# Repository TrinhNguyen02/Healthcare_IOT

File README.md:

# Healthcare_IOT
Overview:
Real time 
IoT Based Patient Health Monitoring System on ESP8266/ESP32 using MAX30100/102 Pulse Oximeter, DS18B20 temperature, DHT11 Humidity & Temperature sensors and display OLED 0.96" . This system will Monitor the Health Status of Patient on ESP8266/ESP32 Web Server.

Reference: 
https://iotprojectsideas.com/iot-based-patient-health-monitoring-system-esp8266-esp32/

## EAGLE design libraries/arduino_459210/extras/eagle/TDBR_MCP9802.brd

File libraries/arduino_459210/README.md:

# MCP9802 DRIVER

&nbsp;&nbsp;&nbsp;&nbsp;&nbsp;&nbsp;&nbsp;&nbsp;&nbsp;&nbsp;

&nbsp;&nbsp;&nbsp;&nbsp;&nbsp;&nbsp;&nbsp;&nbsp;&nbsp;&nbsp;

&nbsp;&nbsp;&nbsp;&nbsp;&nbsp;&nbsp;&nbsp;&nbsp;&nbsp;&nbsp;

## INTRODUCTION

The MCP9802 is a 9 to 12-Bit Single-Channel Temperature Sensor with Hysteresis & Alert capabilities,  
as well as a hardware I2C interface.

This library contains a robust driver for the MCP9802 that exposes its entire functionality (i.e. Configuration, Temperature, Hysteresis, Limit, and Alert Settings), allowing the user to get/set data in degrees Celsius or Fahrenheit.

[MCP9802 DATASHEET](http://ww1.microchip.com/downloads/en/DeviceDoc/21909d.pdf)

[MCP9802 DATASHEET ERRATA](http://ww1.microchip.com/downloads/en/DeviceDoc/80331B.pdf)

## REPOSITORY CONTENTS

- **MCP9802.h** - Library Header file.
- **MCP9802.cpp** - Library Compilation.
- **/utility** 
  - **MCP9802InfoStr.h** - Header file containing a functional extention of the library to include generating printable information String (see Note #8 below).
  - **MCP9802ComStr.h** - Header file containing a functional extention of the library to include generating a printable I2C Communication Result String (see Note #9 below).
  - **MCP9802_PString.h** - Header file for PString class (lighter alternative to String class) 
  - **MCP9802_PString.cpp** - Compilation file for PString class (lighter alternative to String class) 
- **/examples**  
  - **/MCP9802_Test**
    - **MCP9802_Test.ino** - A basic sketch for testing whether the MCP9802 is hooked-up and operating correctly.
  - **/MCP9802_Usage**
    - **MCP9802_Usage.ino** - A much more extensive sketch offering a complete usage illustration, as well as a rubust testing mechanism.
  - **/MCP9802_Info**
    - **MCP9802_Info.ino** - A short sketch showing how to generate a Printable Device Information String of the MCP9802's current settings (i.e. Configuration, Limit &anp; Hysteresis registers, etc.).
  - **/MCP9802_I2C_Status**
    - **MCP9802_I2C_Status.ino** - A short sketch for verifying I2C communication has been established between the controller and the MCP9802.
- **/extras** 
  - **License.txt** - A cope of the end-user license agreement.  
  - **/eagle**
    - **MCP9802.sch** - Schematic file for the MCP9802 breakout board.
    - **MCP9802.brd** - Board layout file for the MCP9802 breakout board.
- **keywords.txt** - Keywords for this library which will be highlighted in sketches within the Arduino IDE. 
- **library.properties** - General library properties for the Arduino's IDE (>1.5) Library Package Manager.
- **README.md** - The readme file for this library.
- **library.json** - JSON file for the Arduino's IDE (>1.5) Package Manager.

## HOOK-UP

* __PIN 1 (VCC)__ - Connect VCC to the Arduino's 5V output
* __PIN 2 (GND)__ - Connect GND to the Arduino's GND
* __PIN 3 (ALERT)__ - Connect ALERT to the Arduino's Digital Pin 2
* __PIN 4 (SCL)__ - Connect SCL to the Arduino's PIN A5 with a 2K2 pull-up resistor
* __PIN 5 (SDA)__ - Connect SDA to the Arduino's PIN A4 with a 2K2 pull-up resistor
* __DECOUPING__: Connect a 0.1uF Ceramic Capacitor between the MCP9802's VCC &amp GND PINS

## GENERAL NOTES

1) __I2C Communications Library Dependency__

This library depends on the Arduino IDE's native '[Wire](https://github.com/arduino/Arduino/tree/master/hardware/arduino/avr/libraries/Wire)' library for I2C communication between the Arduino (Master) and the MCP9802 (Slave). 

2) __Device Temperature Range__

The MCP9802 is designed to measure temperature btween -55°C to 125°C (-67°F to 257°F). Measurments below or above this range will return the minimum or maximum measurable value. Concurently, the ability to custom set the HYSTERESIS or LIMIT values has been limited to this range in software (even though logically, these values would need to be al least slightly lower or higher with respect to the actual measurable temperature). Hence, attempts to set these registers with a new value beyond the said range will actually set the register's value to the maximum/minimum allowable value. 

3) __Standby & Conversion Mode__

The first bit of the configuration byte controls the device mode of operation, namely: ON, in which the device operates in 'CONTINUOUS' mode, or OFF - or more precisely STANDBY (as I2C communication remains active) - in which the device operates in 'SINGLE-SHOT' nmode. As such, setting the 'CONVERSION MODE' of the device to 'CONTINUOUS' will effectively ensure that it is 'ON', while setting it to 'SINGLE-SHOT' mode will turn it into STANDBY mode.

4) __Hysteresis & Limit Registers Resolution__

The Temperature register has a setteble range of 9 to 12-BIT (0.5 to 0.0625 degrees Celsius respectively). However, both the LIMIT and HYSTERESIS registers only have a 9-BIT fixed resolution. This means these registers can only be set with a maximum accuracy of 0.5 degrees Celsius. Hence, while the relevant functions (i.e. setHyst() and setLimit() ) will happily accept any float value within the premmitted parameter range (-55°C to 125°C) for either of these two registers, this float value will be automatically rounded to the nearest 0.5C.

5) __Degrees Celsius & Fahrenheit__

The libraty offers the option of getting/setting all termperature values (Abmient [read-only], Limit [read-write] and/or Hysteresis [read-write]) in either degrees Celsuis or Fahrenheit (the default is degrees Celsius).

6) __Degrees Fahrenheit Accuracy Limitation__

As the MCP9802 was designed to work in a degrees Celsuis scheme, all Fahrenheit values obtained (or custom set by the user) can only represent as close approximations as possible with relation to the Celsius values generated or stored by the device. This limitation is perhaps most noticable when setting the LIMIT or HYSTERESIS registers to custom Fahrenheit values, as a double operation needs to take place, namely: conversion of this figure to the equivalent Celsius value and then rounding that value to the nearest 0.5 degree Celisus (the latter stems from the 9-BIT size of the HYSTERESIS & LIMIT registers as noted above).

7) __Alert Output Signal__

The MCP9802's Alert functionality is based on an 'open collector' architecture which means it requires a pull-up resistor in order to work (this is true for both Alert Types, i.e. 'ACTIVE-LOW' and 'ACTIVE-HIGH). For the purposes of this testing sketch, the Atmega's (weak) internal pull-up resistor is used and so the only connection needed in this context is between the MCP9802's ALERT pin and the Arduino's Digital Pin D2. However, for any real-life use of the device, it is highly recommended to implement a suitable external pull-up resistor (typically 10K) hooked-up betweem the ALERT pin and VCC.

8) __Device Information String__

It is now possible to extend the MCP9802 Library to include a function for generating a pritable device information string showing all the relevant details about the devices current Configuration, Limit & Hysteresis settings. As the additional functionality comes at the cost of increased memory footprint, it was implemented as an optional add-on rather than added directly to the core MCP9802 Library. See the [MCP9802_Info](https://github.com/nadavmatalon/MCP9802/blob/master/examples/MCP9802_Info/MCP9802_Info.ino) example sketch for detailed explanation and an actual usage demo.

9) __Device I2C Communications String__

It is now possible to also extend the MCP9802 Library to include a function for generating a pritable I2C Communications string showing the result of each I2C transaction in a human-friendly way, something that may be useful, for example, during debugging sessions. As the additional functionality comes at the cost of increased memory footprint, it was implemented as an optional add-on rather than added directly to the core MCP9802 Library. See the [MCP9802_I2C_Status](https://github.com/nadavmatalon/MCP9802/blob/master/examples/MCP9802_I2C_Status/MCP9802_I2C_Status.ino) example sketch for detailed explanation and an actual usage demo.

## I2C ADDRESSES

Each MCP9802 has 1 of 8 possible I2C addresses (factory hardwired & recognized by its specific part number & top marking on the package itself):

| PART NO.        | BIN      | HEX  | DEC | MARKING |
|-----------------|----------|------|-----|---------|
| MCP9802A0T-M/OT | 01001000 | 0x48 | 72  | JKNN    |
| MCP9802A1T-M/OT | 01001001 | 0x49 | 73  | JLNN    |
| MCP9802A2T-M/OT | 01001010 | 0x4A | 74  | JMNN    |
| MCP9802A3T-M/OT | 01001011 | 0x4B | 75  | JPNN    |
| MCP9802A4T-M/OT | 01001100 | 0x4C | 76  | JQNN    |
| MCP9802A5T-M/OT | 01001101 | 0x4D | 77  | JRNN    |
| MCP9802A6T-M/OT | 01001110 | 0x4E | 78  | JSNN    |
| MCP9802A7T-M/OT | 01001111 | 0x4F | 79  | JTNN    |

## LIBRARY INSTALLATION & SETUP

Begin by installing the library either by using the Arduino IDE's Installation Wizard (Arduino Version >1.5) or simply download the library's ZIP folder from GITHUB, extract it, and copy the extraxcted folder to your Arduino 'libraries' folder.

Next, include the library at the top of the sketch as follows:

```
#include "MCP9802.h"
```

At this point you can construct a new MPC9802 object(s) by using the following command (at the top of the sketch after the 'include' line):

```
MCP9802 device_name(device_address);
```

>__NOTE__: replace the '__device_name__' above with a name of your choice. Also, make sure to replace the variable '__device_address__' with the specific I2C address of your device - see I2C ADDRESSES section above.

## LIBRARY FUNCTIONS

With the library installed & included in the sketch, and an MCP9802 object initiallized, the following functions are available (see the usage example sketch for a detailed implementation):

__Note About Methods' Return Values:__  
All 'get' methods return some sort of value (e.g. temp reading, hysteresis setting, etc.), while all 'set' methods return nothing. Nevertheless, ALL methods implicitly update the library's __I2C _comBuffer__ (=communication buffer) after each I2C transmission. The reason for this functional design is to maintain structural coherance between the 'get' and 'set' methods. As 'get' methods cannot return both the desired value and the I2C transmission's result simultaniously. Consequently, if the relevant value hasn't been obtained by a particular 'get' method, the user can simply check the content of the _comBuffer to see what error occured. Similarly, it is possible to check if a particular setting has been successfully applied via a 'set' method either by preforming the corresponding 'get' method - e.g. getHystC() after using setHystC() - or by checking the content of the _comBuffer (0 indicates a successful transmission, 1-6 indicate an error as listed below). 

__ping();__                                  
Parameters:&nbsp;&nbsp;&nbsp;None  
Description:&nbsp;&nbsp;&nbsp;Searches for the MCP9802 at the pre-defined I2C Bus address &amp; returns byte with the relevant success/error code, as follows:  
0  ... Success (no error)  
1  ... Buffer overflow  
2  ... Address sent, NACK received  
3  ... Data send, NACK received  
4  ... Other error (lost bus arbitration, bus error, etc.)  
5  ... Timed-out while trying to become Bus Master  
6  ... Timed-out while waiting for data to be sent
>6 ... Unlisted error (potential future implementation/s)<br>

Returns:&nbsp;&nbsp;&nbsp;&nbsp;&nbsp;&nbsp;&nbsp;&nbsp;&nbsp;byte  

__getTemp();__  
Parameters:&nbsp;&nbsp;&nbsp;None  
Description:&nbsp;&nbsp;&nbsp;Returns current temperature reading in degrees Celsius  
Returns:&nbsp;&nbsp;&nbsp;&nbsp;&nbsp;&nbsp;&nbsp;&nbsp;&nbsp;&nbsp;float

__getHyst();__  
Parameters:&nbsp;&nbsp;&nbsp;None  
Description:&nbsp;&nbsp;&nbsp;Returns the current Hysteresis register value in degrees Celsius   
Returns:&nbsp;&nbsp;&nbsp;&nbsp;&nbsp;&nbsp;&nbsp;&nbsp;&nbsp;float

__getLimit();__  
Parameters:&nbsp;&nbsp;&nbsp;None  
Description:&nbsp;&nbsp;&nbsp;Returns the current Limit register value in degrees Celsius    
Returns:&nbsp;&nbsp;&nbsp;&nbsp;&nbsp;&nbsp;&nbsp;&nbsp;&nbsp;float

__getAlertType();__  
Parameters:&nbsp;&nbsp;&nbsp;None  
Description:&nbsp;&nbsp;&nbsp;Returns the current alert type setting (0 = COMPARATOR / 1 = INTERRUPT)  
Returns:&nbsp;&nbsp;&nbsp;&nbsp;&nbsp;&nbsp;&nbsp;&nbsp;&nbsp;byte

__getAlertMode();__  
Parameters:&nbsp;&nbsp;&nbsp;None  
Description:&nbsp;&nbsp;&nbsp;Returns the current alert mode setting (0 = ACTIVE-LOW / 1 = ACTIVE-HIGH)  
Returns:&nbsp;&nbsp;&nbsp;&nbsp;&nbsp;&nbsp;&nbsp;&nbsp;&nbsp;None

__getFaultQueue();__  
Parameters:&nbsp;&nbsp;&nbsp;None  
Description:&nbsp;&nbsp;&nbsp;Returns the current Fault Queue setting (1 / 2 / 4 / 6 fault readings - i.e. below Hysteresis or above the Limit - before activating the alert)  
Returns:&nbsp;&nbsp;&nbsp;&nbsp;&nbsp;&nbsp;&nbsp;&nbsp;&nbsp;&nbsp;byte

__getResolution();__  
Parameters:&nbsp;&nbsp;&nbsp;None  
Description:&nbsp;&nbsp;&nbsp;Returns the current Resolution setting (9 = 9-BIT / 10 = 10-BIT / 11 = 11-BIT / 12 = 12-BIT)  
Returns:&nbsp;&nbsp;&nbsp;&nbsp;&nbsp;&nbsp;&nbsp;&nbsp;&nbsp;byte

__getConMode();__  
Parameters:&nbsp;&nbsp;&nbsp;None  
Description:&nbsp;&nbsp;&nbsp;Returns the current Conversion Mode setting (0 = CONTINUOUS / 1 = SINGLE-SHOT)  
Returns:&nbsp;&nbsp;&nbsp;&nbsp;&nbsp;&nbsp;&nbsp;&nbsp;&nbsp;byte

__getTempUnit();__  
Parameters:&nbsp;&nbsp;&nbsp;None  
Description:&nbsp;&nbsp;&nbsp;Returns the current Degrees Unit setting (0 = CELSIUS / 1 = FAHRENHEIT)  
Returns:&nbsp;&nbsp;&nbsp;&nbsp;&nbsp;&nbsp;&nbsp;&nbsp;&nbsp;byte

__singleCon();__  
Parameters:&nbsp;&nbsp;&nbsp;None   
Conditions:&nbsp;&nbsp;&nbsp;&nbsp;Works only in __Single-Shot__ mode  
Description:&nbsp;&nbsp;&nbsp;Carries out a single conversion &amp; returns a temperature reading in degrees Celsius  
Returns:&nbsp;&nbsp;&nbsp;&nbsp;&nbsp;&nbsp;&nbsp;&nbsp;&nbsp;float

__setHyst();__  
Parameters:&nbsp;&nbsp;&nbsp;int / float (range: -55 to +125)  
Description:&nbsp;&nbsp;&nbsp;Sets the Hysteresis register value in degrees Celsius  
Returns:&nbsp;&nbsp;&nbsp;&nbsp;&nbsp;&nbsp;&nbsp;&nbsp;&nbsp;None

__setLimit();__  
Parameters:&nbsp;&nbsp;&nbsp;int / float (range: -55 to +125)  
Description:&nbsp;&nbsp;&nbsp;Sets the Limit register value in degrees Celsius   
Returns:&nbsp;&nbsp;&nbsp;&nbsp;&nbsp;&nbsp;&nbsp;&nbsp;&nbsp;None

__setAlertType();__  
Parameters:&nbsp;&nbsp;&nbsp;COMP / INT  
Description:&nbsp;&nbsp;&nbsp;Sets the alert output type (COMPARATOR / INTERRUPT)  
Returns:&nbsp;&nbsp;&nbsp;&nbsp;&nbsp;&nbsp;&nbsp;&nbsp;&nbsp;None

__setAlertMode();__  
Parameters:&nbsp;&nbsp;&nbsp;ACTIVE_LOW / ACTIVE_HIGH  
Description:&nbsp;&nbsp;&nbsp;Sets the alert output mode (ACTIVE-LOW / ACTIVE-HIGH)  
Returns:&nbsp;&nbsp;&nbsp;&nbsp;&nbsp;&nbsp;&nbsp;&nbsp;&nbsp;None

__setFaultQueue();__  
Parameters:&nbsp;&nbsp;&nbsp;FQ1 / FQ2 / FQ4 / FQ6  
Description:&nbsp;&nbsp;&nbsp;Sets the Fault Queue value (FQ1 = 1 Fault / FQ2 = 2 Faults / FQ4 = 4 Faults / FQ6 = 6 Faults)  
Returns:&nbsp;&nbsp;&nbsp;&nbsp;&nbsp;&nbsp;&nbsp;&nbsp;&nbsp;None

__setResolution();__  
Parameters:&nbsp;&nbsp;&nbsp;RES_9 / RES_10 / RES_11 / RES_12  
Description:&nbsp;&nbsp;&nbsp;Sets the Resolution value (RES_9 = 9-BIT / RES_10 = 10-BIT / RES_11 = 11-BIT / RES_12 = 12-BIT)  
Returns:&nbsp;&nbsp;&nbsp;&nbsp;&nbsp;&nbsp;&nbsp;&nbsp;&nbsp;None

__setConMode();__  
Parameters:&nbsp;&nbsp;&nbsp;CONT / SINGLE  
Description:&nbsp;&nbsp;&nbsp;Sets the Conversion Mode (CONTINUOUS / SINGLE-SHOT)  
Returns:&nbsp;&nbsp;&nbsp;&nbsp;&nbsp;&nbsp;&nbsp;&nbsp;&nbsp;None

__setTempUnit();__  
Parameters:&nbsp;&nbsp;&nbsp;CELSIUS / FAHRENEHIT  
Description:&nbsp;&nbsp;&nbsp;Sets the Degree Unit type (CELSIUS / FAHRENEHIT)  
Returns:&nbsp;&nbsp;&nbsp;&nbsp;&nbsp;&nbsp;&nbsp;&nbsp;&nbsp;None

__reset();__  
Parameters:&nbsp;&nbsp;&nbsp;None  
Description:&nbsp;&nbsp;&nbsp;Resets the device to power-up default settings (except for the TEMP Register which is Read-Only), as follows:

* REG POINTER: 0x00 (TEMP REGISTER)
* CONFIG: 0x00
* DEVICE MODE: ON
* ALERT OUTPUT TYPE: COMPARATOR
* ALERT OUTPUT MODE: ACTIVE-LOW
* FAULT-QUEUE: 1 FAULT
* RESOLUTION: 9-BIT
* CONVERSION MODE: CONTINUOUS
* DEGREES TYPE: CELSIUS
* HYSTERESIS: 0x9600 (75°C)
* LIMIT: 0xA000 (80°C)

Returns:&nbsp;&nbsp;&nbsp;&nbsp;&nbsp;&nbsp;&nbsp;&nbsp;&nbsp;None

__getComResult();__  
Parameters:&nbsp;&nbsp;&nbsp;None  
Description:&nbsp;&nbsp;Returns the latest I2C Communication result code (see Success/Error codes above)  
Returns:&nbsp;&nbsp;&nbsp;&nbsp;&nbsp;&nbsp;&nbsp;&nbsp;byte

__Destructor__  
If you want to destruct an instantiated MCP9802 object, you can use the following method to do so:

```
~MCP9802 device_name();
```
>__NOTE__: replace the '__device_name__' above with the name of your MCP9802 device.

## Extended Functionality*

(* requires an additional '\#include' of the relevant *.h file as shown in the corresponding example sketches)

__MCP9802ComStr();__  
Parameters:&nbsp;&nbsp;&nbsp;Name of an initialized MCP9802 instance  
Description:&nbsp;&nbsp;Returns printable string containing human-friendly information about the device's latest I2C communication result  
Returns:&nbsp;&nbsp;&nbsp;&nbsp;&nbsp;&nbsp;&nbsp;&nbsp;PString

__MCP9802InfoStr();__  
Parameters:&nbsp;&nbsp;&nbsp;Name of an initialized MCP9802 instance  
Description:&nbsp;&nbsp;Returns printable string containing detailed information about the device's current settings   
Returns:&nbsp;&nbsp;&nbsp;&nbsp;&nbsp;&nbsp;&nbsp;&nbsp;PString

## RUNNING THE EXAMPLE SKETCHES

1) Hook-up the MCP9802 to the Arduino as explained above.   
2) Upload the relevant example sketch to the Arduino.  
3) Open the Serial Communications Window (make sure the baud-rate is set to 9600 or change it in the sketch to match your Serial Port's buad-rate).  

## BUG REPORTS

Please report any issues/bugs/suggestions at the [Issues](https://github.com/nadavmatalon/MCP9802/issues) section of this Github repository.

## TODO

* __CORE LIBRARY__: add emptyBuffer() function and amend I2C communication functions to include 3 attempts to get data
* __CORE LIBRARY__: Change setX() functions to work with bitMasks (?)
* __CORE LIBRARY__: Create interger-math methods for getting/setting Temp/Hyst/Limit   
* __CORE LIBRARY__: Add running average functionality  

## VERSION HISTORY

__Ver. 1.0.0__ - First release (26.9.16)  
__Ver. 1.1.0__ - Small change in functionality: attempting to set hysteresis or limit beyond the legitimate range (-55°C - 125°C / -67°F - 257°F) now sets the register to the maximum/minumum allowable value rather than do nothing (4.10.16)  
__Ver. 1.2.0__ - Changed license to MIT (5.10.16)  
__Ver. 1.3.0__ - Changed auxilliary functions: MCP9802InfoStr() and MCP9802ComStr() to work with the PString class instead of the String class to further reduce memory footprint. For this purpose, added PString.h & PString.cpp files to /utility folder. In addition added "I2C STATUS" (CONNECTED / NOT CONNECTED) field to device information string (9.10.16)  
__Ver. 1.4.0__ - Added namespaces to prevent conflicts with other libraries (15.10.16)  
__Ver. 1.5.0__ - Switched from 'WSWire' library to 'Wire' library for I2C communications (24.10.16)

## LICENSE

[The MIT License (MIT)](https://opensource.org/licenses/MIT)
Copyright (c) 2016 Nadav Matalon

Permission is hereby granted, free of charge, to any person obtaining a copy of this software and associated documentation files (the "Software"), to deal in the Software without restriction, including without limitation the rights to use, copy, modify, merge, publish, distribute, sublicense, and/or sell copies of the Software, and to permit persons to whom the Software is furnished to do so, subject to the following conditions:

The above copyright notice and this permission notice shall be included in all copies or substantial portions of the Software.

THE SOFTWARE IS PROVIDED "AS IS", WITHOUT WARRANTY OF ANY KIND, EXPRESS OR IMPLIED, INCLUDING BUT NOT LIMITED TO THE WARRANTIES OF MERCHANTABILITY, FITNESS FOR A PARTICULAR PURPOSE AND NONINFRINGEMENT. IN NO EVENT SHALL THE AUTHORS OR COPYRIGHT HOLDERS BE LIABLE FOR ANY CLAIM, DAMAGES OR OTHER LIABILITY, WHETHER IN AN ACTION OF CONTRACT, TORT OR OTHERWISE, ARISING FROM, OUT OF OR IN CONNECTION WITH THE SOFTWARE OR THE USE OR OTHER DEALINGS IN THE SOFTWARE.

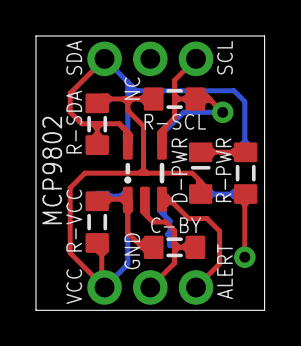
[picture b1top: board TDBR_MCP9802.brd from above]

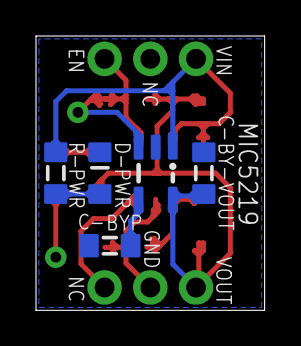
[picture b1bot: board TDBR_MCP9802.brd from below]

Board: 2 copper layers, 12.7 x 15.2 mm, 13 parts (5 on the bottom side), 9 nets.

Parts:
MCP9802: MCP9802A0T-M/OT; SOT-23-5
MCP9802-C-BY: (100nF/50V, X7R, 5%, 08055C104J4Z2A); 0805
MCP9802-D-LED: (GREEN, HSMG-C170); DIODE_0805
MCP9802-J1: HEADER_6_PIN; HEADER_2.54MM_6_PIN_VER
MCP9802-R-LED: (1K/0.5W, 1%, ERJ-P06F1001V); 0805
MCP9802-R-SCL, MCP9802-R-SDA: (2K2/0.25W, 5%, ERJ-T06J222V); 0805
MCP9802-R-VCC: (200R/0.5W, 1%, ERJ-P06F2000V); 0805
VREG-C-BP1: (2.2uF/50V, X7R, 10%, CGA4J3X7R1H225K125AE); 0805
VREG-C-BP2: (470pF/50V, C0G (NP0), 5%, C0805C471J5GACAUTO); 0805
VREG-D-LED: (GREEN, HSMG-C170); DIODE_0805
VREG-MIC5219: MIC5219-5.0YM5-TR; SOT-23-5
VREG-R-LED: (1K/0.5W, 1%, ERJ-P06F1001V); 0805

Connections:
MCP9802-ALERT: MCP9802.3, MCP9802-J1.3
MCP9802-FILTERED-VCC: MCP9802.1, MCP9802-C-BY.1, MCP9802-R-VCC.2
MCP9802-GND: MCP9802.2, MCP9802-C-BY.2, MCP9802-J1.2, MCP9802-R-LED.1, VREG-C-BP1.1, VREG-C-BP2.1, VREG-D-LED.C, VREG-MIC5219.2
MCP9802-LED: MCP9802-D-LED.C, MCP9802-R-LED.2
MCP9802-SCL: MCP9802.4, MCP9802-J1.4, MCP9802-R-SCL.1, VREG-MIC5219.3
MCP9802-SDA: MCP9802.5, MCP9802-J1.6, MCP9802-R-SDA.1, VREG-MIC5219.1, VREG-R-LED.2
MCP9802-VCC: MCP9802-D-LED.A, MCP9802-J1.1, MCP9802-R-SCL.2, MCP9802-R-SDA.2, MCP9802-R-VCC.1, VREG-C-BP1.2, VREG-MIC5219.5
MCP9802-VREG-BYP: VREG-C-BP2.2, VREG-MIC5219.4
MCP9802-VREG-LED: VREG-D-LED.A, VREG-R-LED.1

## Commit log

2023-03-29 finally
2023-03-29 fixed conflict MAX30100
2023-03-31 Description

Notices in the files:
libraries/arduino_459210/README.md:
LICENSE:
[The MIT License (MIT)](https://opensource.org/licenses/MIT)
Copyright (c) 2016 Nadav Matalon
Permission is hereby granted, free of charge, to any person obtaining a copy of this software and associated documentation files (the "Software"), to deal in the Software without restriction, including without limitation the rights to use, copy, modify, merge, publish, distribute, sublicense, and/or sell copies of the Software, and to permit persons to whom the Software is furnished to do so, subject to the following conditions: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
MIT License
